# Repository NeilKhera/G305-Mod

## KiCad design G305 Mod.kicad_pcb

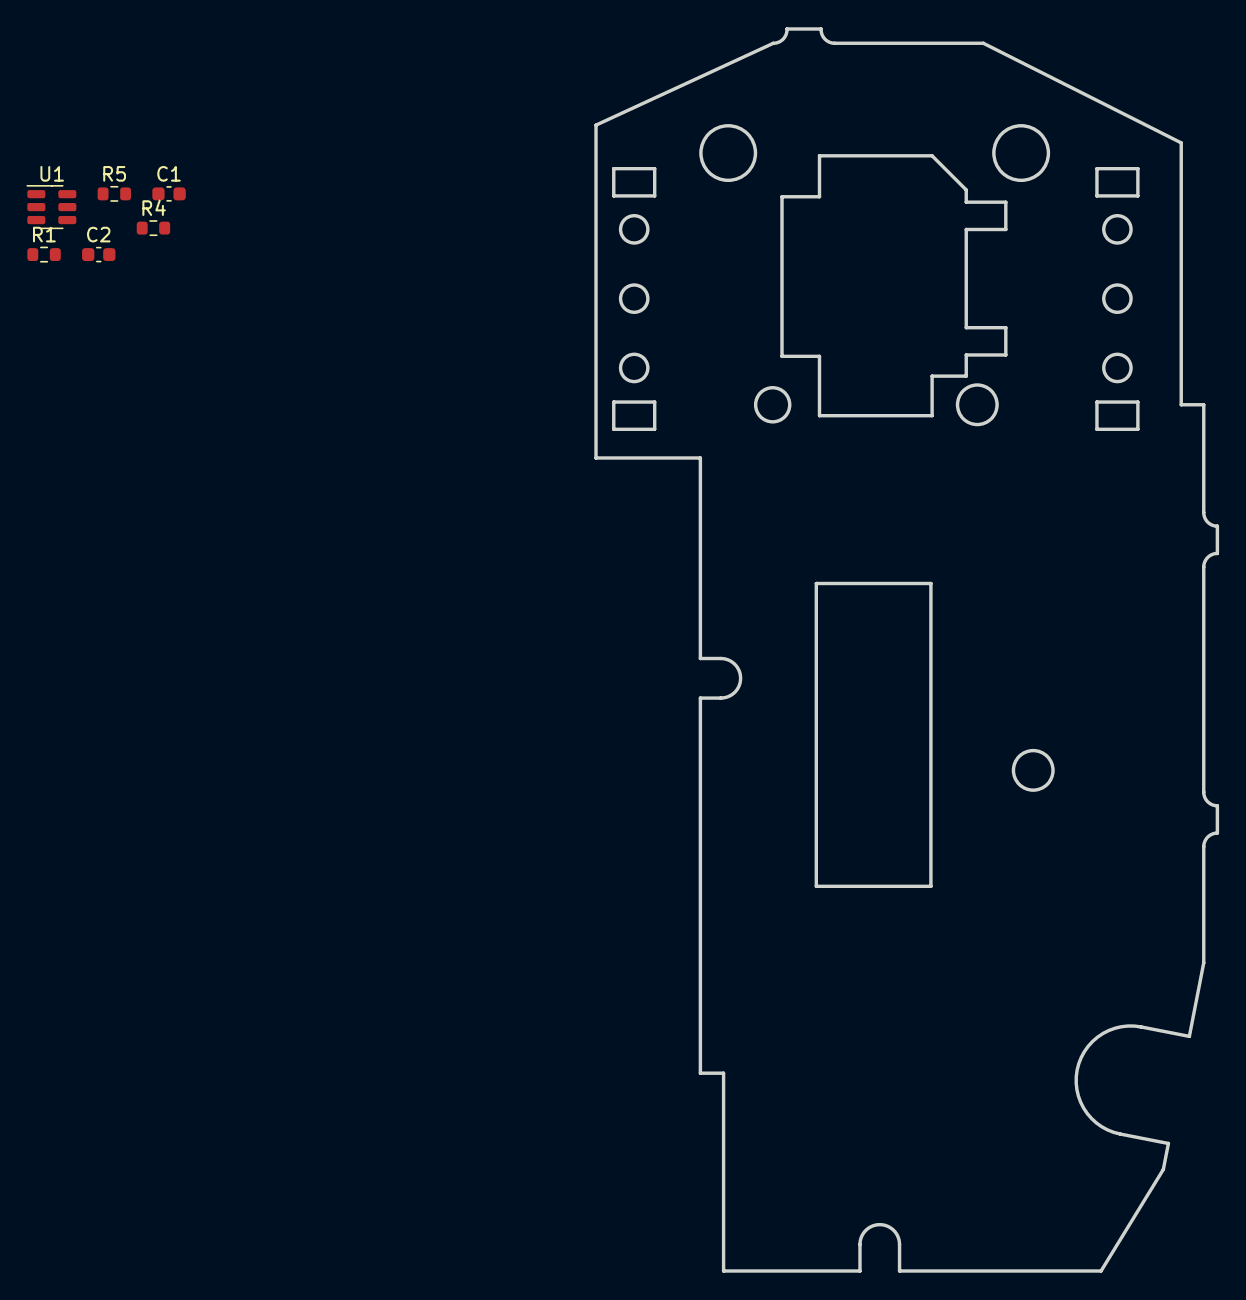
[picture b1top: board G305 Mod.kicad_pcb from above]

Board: 2 copper layers, 45.5 x 91.0 mm, 6 parts (0 on the bottom side), 5 nets, no tracks yet.

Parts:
C1: 4.7nF; C_0603_1608Metric
C2: 0.1uF; C_0603_1608Metric
R1: 1M; R_0603_1608Metric
R4, R5: 22; R_0603_1608Metric
U1: USBLC6-2SC6; SOT-23-6

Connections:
/DN: R5.2, U1.4 (I/O2)
/DP: R4.1, U1.6 (I/O1)
/SHIELD: C1.2, R1.2
GND: C1.1, C2.1, R1.1, U1.2 (GND)
VBUS: C2.2, U1.5 (VBUS)

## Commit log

2023-06-20 File upload
